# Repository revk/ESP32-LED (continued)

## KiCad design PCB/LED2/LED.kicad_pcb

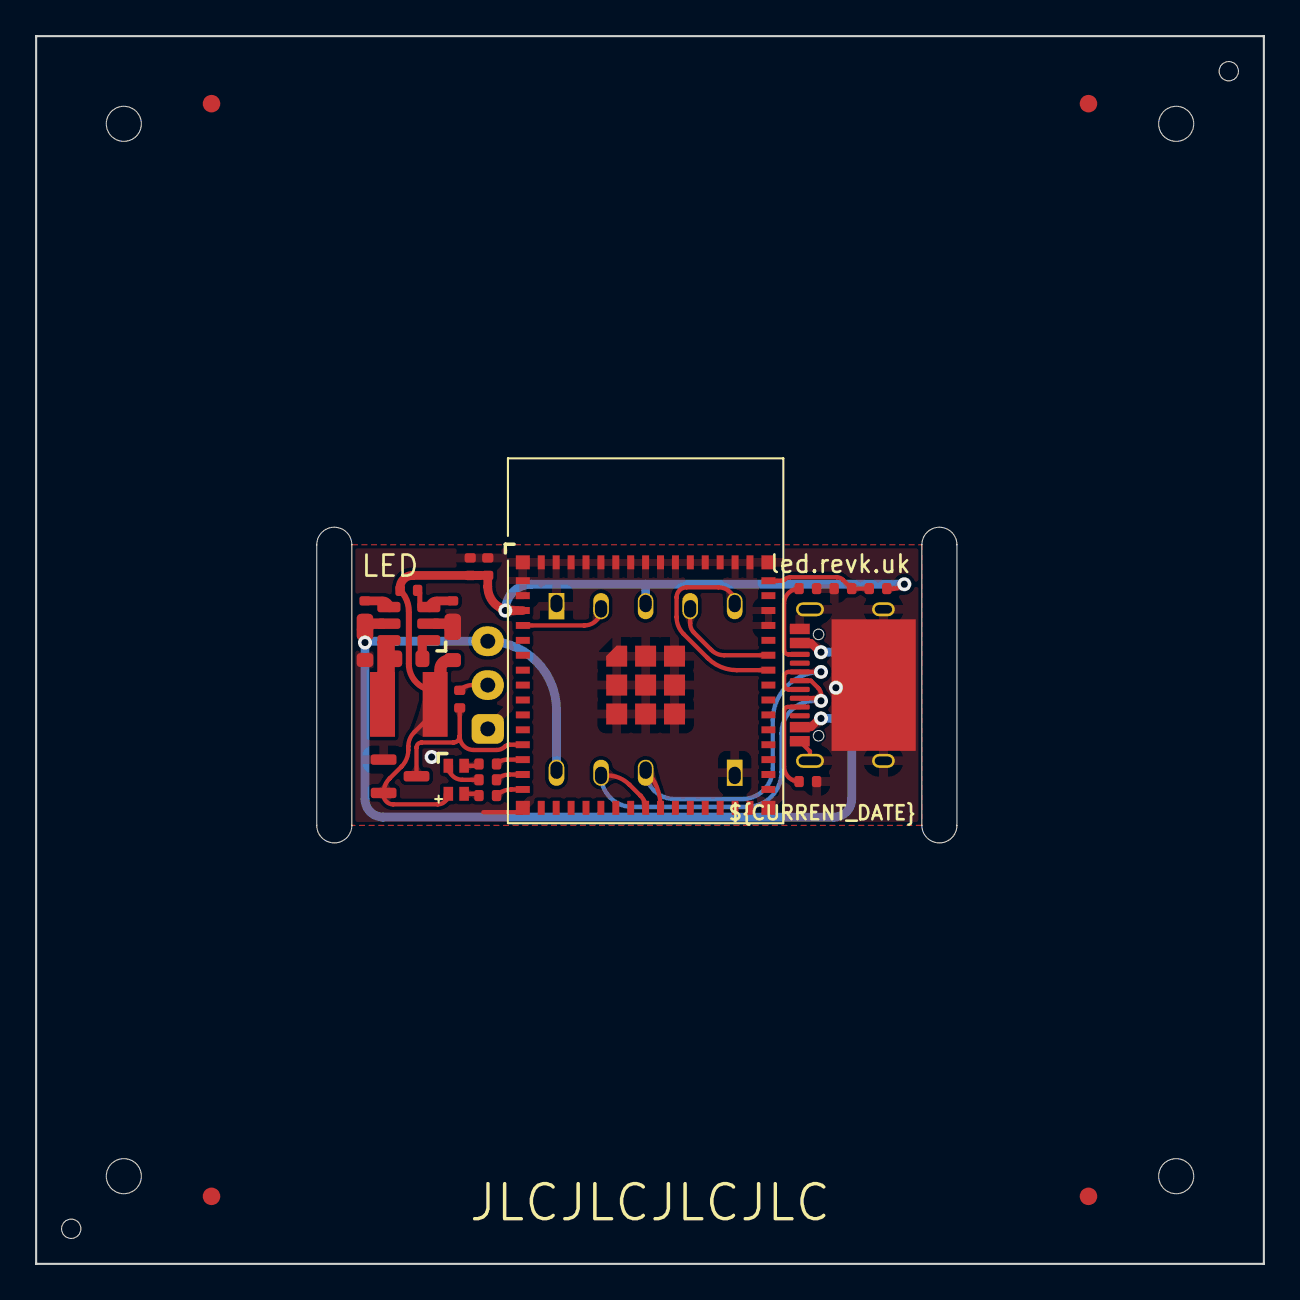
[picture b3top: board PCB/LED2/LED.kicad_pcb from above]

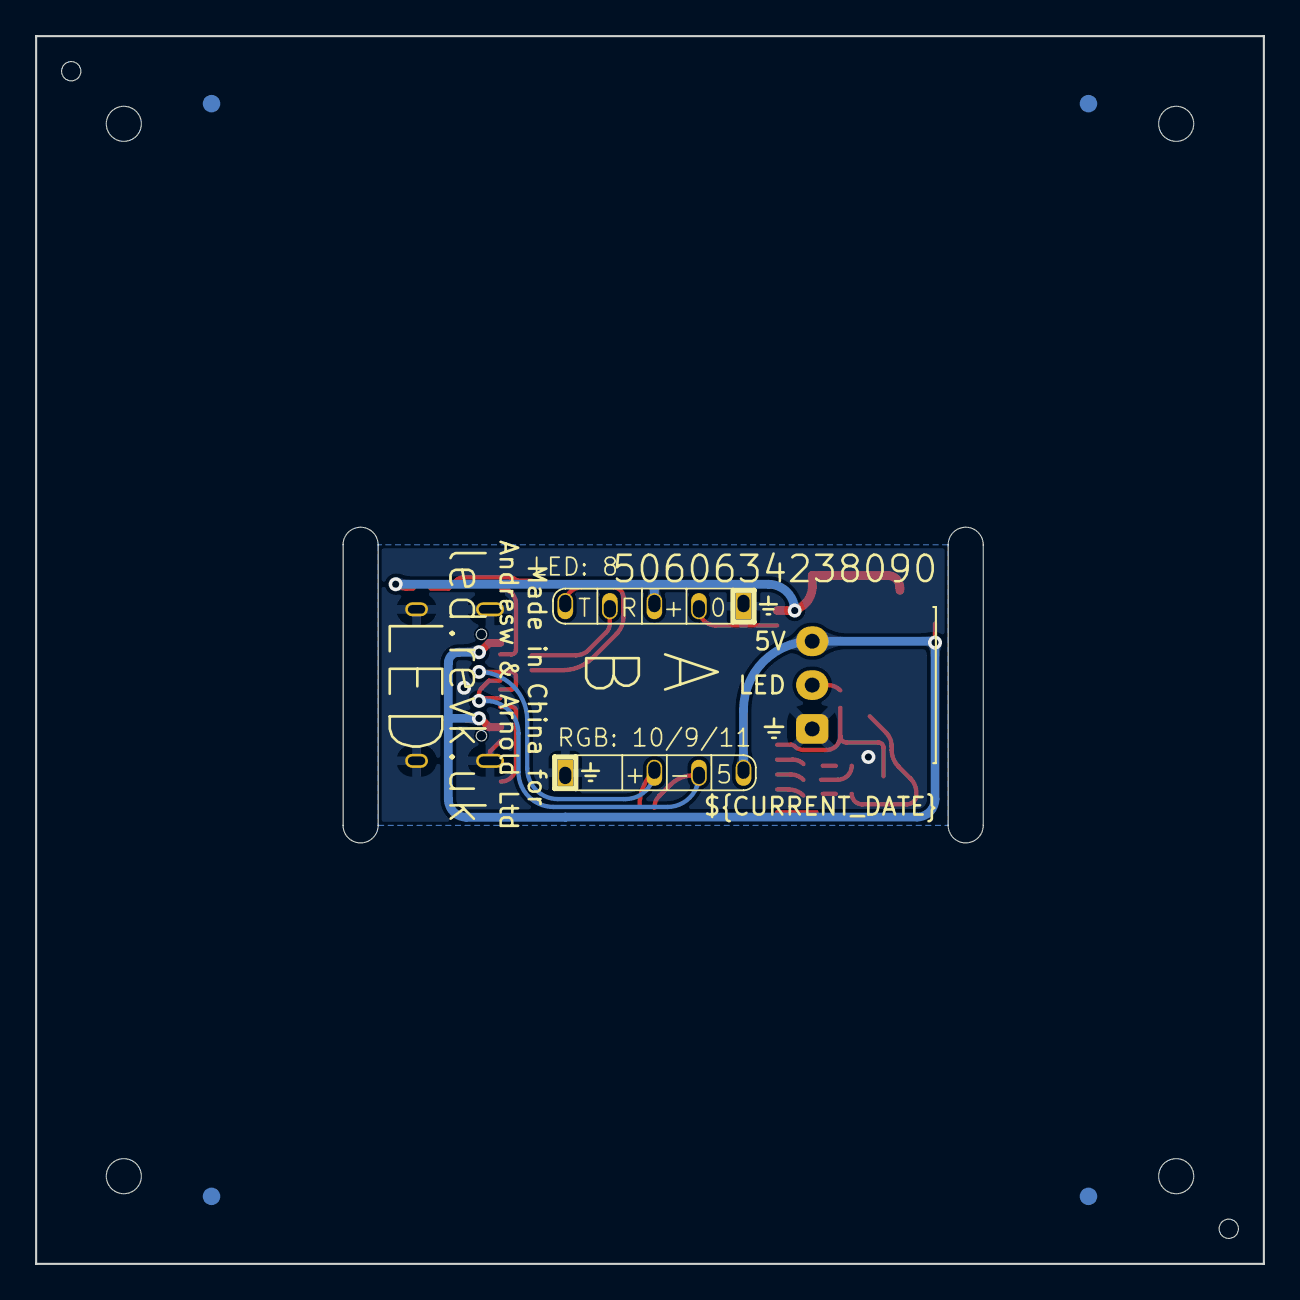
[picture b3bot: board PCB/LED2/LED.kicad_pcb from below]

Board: 2 copper layers, 70.0 x 70.0 mm, 28 parts (3 on the bottom side), 19 nets.

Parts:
C7: 100nF; C_0402
C8: 22uF; C_0402
C9: 1uF; C_0402
C10: 10uF 50V; C_0603_
C11: 10uF 6.3V; C_0603_
C12: 100nF; C_0603_
D2: RGB; LED-RGB-1.6x1.6
D3: BAV99; SOT-23
J1: Conn_01x03; PTSM-HH-3-RA
J2: USB-C; USC16-TR
J3: Shelly
J4: USB-PROG
L2: 10uH; L_4x4_
PCB1: 70x70; PCB7070
R2: 10K; R_0402
R4: 124k; R_0402_
R5, R6: 5K1; R_0402
R7: 100R; R_0402
R8: 680R; R_0402
R11: 2K; R_0402
R12: 220R; R_0402
R14: 39k2; R_0402_
R15: 1M; R_0402_
U6: ESP32-S3-MINI-1
U7: MD8942; SOT-23-6-MD8942
V1, V2: VCUT70

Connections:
+3V3: C7.1, C8.1, D2.4 (A), D3.2 (A), J3.3 (3V3), R2.1, U6.3 (3V3), U7.8 (VOUT)
B: R12.2, U6.15 (GPIO11)
D+: J2.A6 (D+), J2.B6 (D+), J4.3 (D+), U6.24 (GPIO20)
D-: J2.A7 (D-), J2.B7 (D-), J4.2 (D-), U6.23 (GPIO19)
DC: J1.3, J2.A4 (VBUS), J2.A9 (VBUS), J2.B4 (VBUS), J2.B9 (VBUS), J4.1 (VBUS), U7.5 (VIN)
G: R11.2, U6.13 (GPIO9)
GND: C7.2, C8.2, C9.2, D3.1 (K), J1.1, J2.A1 (GND), J2.A12 (GND), J2.B1 (GND), J2.B12 (GND), J2.S1 (SHIELD), J3.1 (GND), J4.4 (GND), R5.2, R6.1, U6.1 (GND), U6.2 (GND), U6.42 (GND), U6.43 (GND), U6.46 (GND), U6.47 (GND), U6.48 (GND), U6.49 (GND), U6.50 (GND), U6.51 (GND), U6.52 (GND), U6.53 (GND), U6.54 (GND), U6.55 (GND), U6.56 (GND), U6.57 (GND), U6.58 (GND), U6.59 (GND), U6.60 (GND), U6.61 (GND), U6.62 (GND), U6.63 (GND), U6.64 (GND), U6.65 (GND), U7.2 (GND), U7.7 (GND)
LED: D3.3 (K), R7.2, U6.12 (GPIO8)
unnamed: D2.3 (BK), R12.1
unnamed: D2.2 (GK), R11.1
unnamed: D2.1 (RK), R8.1
unnamed: J1.2, R7.1
unnamed: J2.A5 (CC1), R5.1
unnamed: J2.B5 (CC2), R6.2
unnamed: J3.2 (0), U6.4 (GPIO0)
unnamed: J3.4 (Rx), U6.40 (GPIO44)
unnamed: J3.5 (Tx), U6.39 (GPIO43)
unnamed: C9.1, R2.2, U6.45 (EN)
R: R8.2, U6.14 (GPIO10)

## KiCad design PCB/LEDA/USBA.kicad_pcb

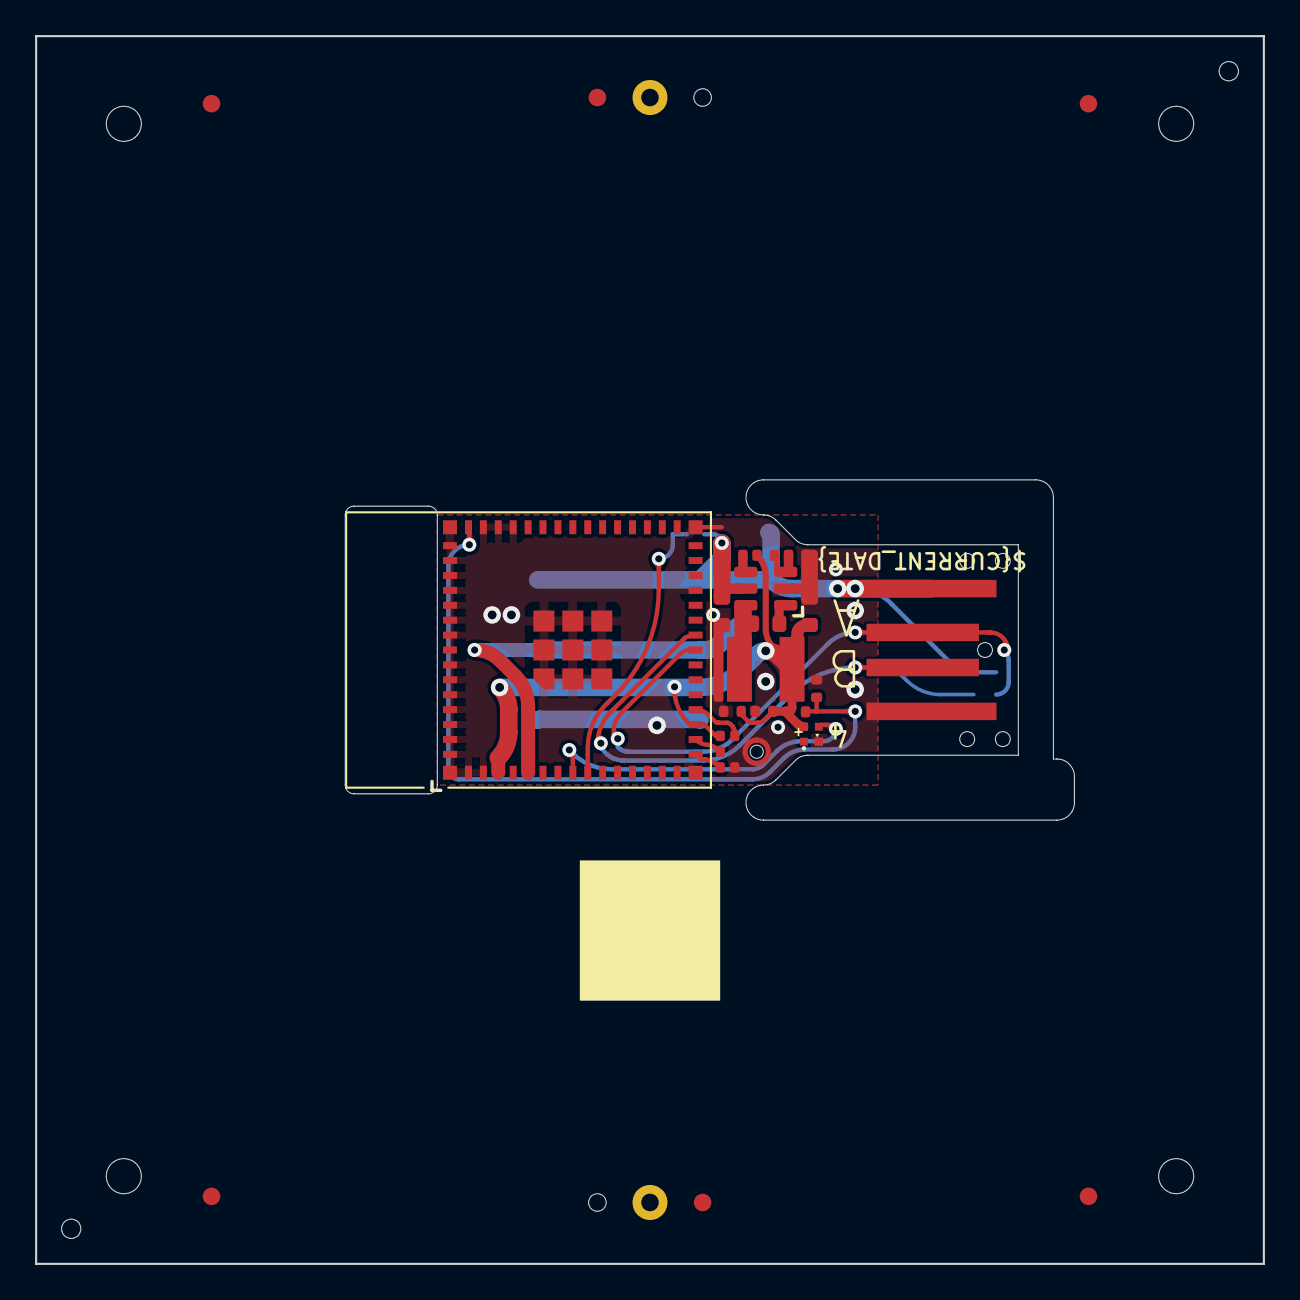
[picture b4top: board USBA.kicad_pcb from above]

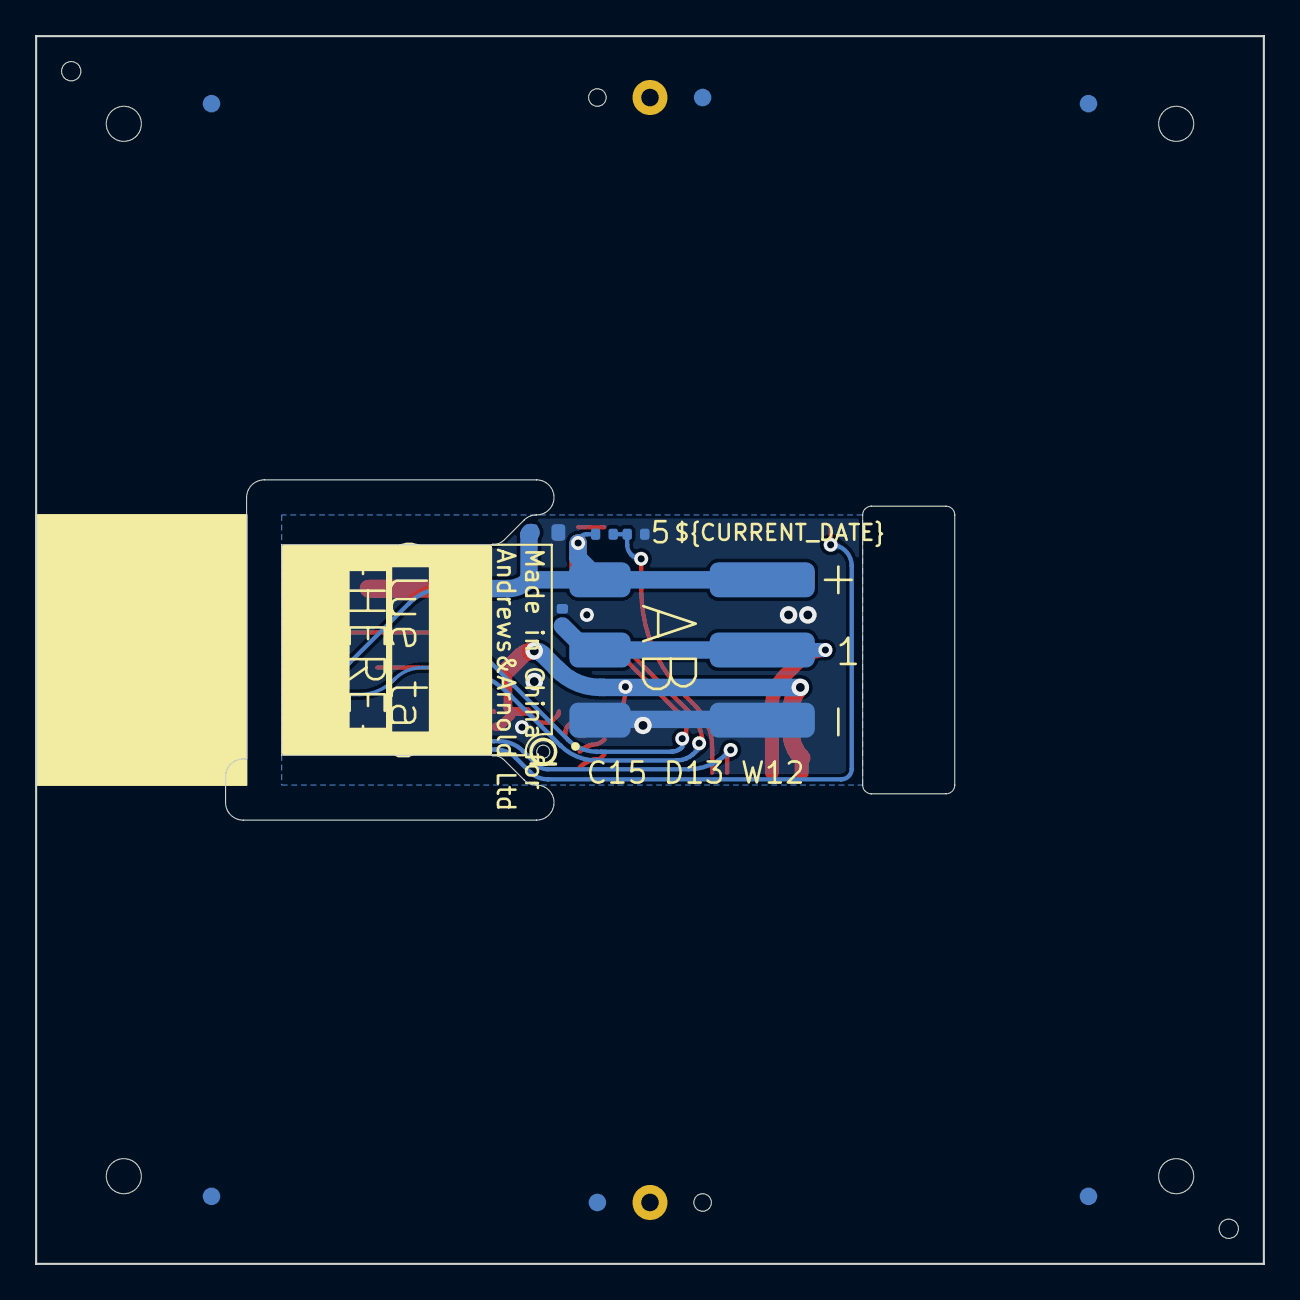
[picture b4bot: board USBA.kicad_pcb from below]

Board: 2 copper layers, 70.0 x 70.0 mm, 25 parts (8 on the bottom side), 12 nets.

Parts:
C1: 100nF; C_0402
C2: 22uF; C_0402
C3: 1uF; C_0402
C4: 10uF 35V; C_0603
C6: 10uF 35V; C_0603_
C7: 10uF 6.3V; C_0603_
C8: 100nF; C_0603_
D1: XL-1010RGBC-WS2812B; SMD1010
D2: DFN1006-2L
J1: USB_A; USB-A-PCB
J2: Conn_01x03; WAGO-2060-453-998-404
J3: TC2030-USB-NL-DS; Tag-Connect_TC2030-IDC-NL_2x03_P1.27mm_Vertical
L2: 10uH; L_4x4_
PCB1: 70x70; PCB7070
R1, R3: 10K; R_0402
R2: 124K; R_0402
R9: 124k; R_0402_
R10: 39k2; R_0402_
R11: 1M; R_0402_
U1: ICS43434_MEMS_Mic
U2: ESP32-S3-MINI-1
U5: MD8942; SOT-23-6-MD8942
V1, V2: 70; VCUT70N

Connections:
+3.3V: C1.1, C2.1, D1.2 (+), R1.1, U1.5 (VDD), U2.3 (3V3), U2.18 (GPIO14), U5.8 (VOUT)
ADC: R2.2, R3.1, U2.9 (GPIO5)
D+: J1.3 (D+), J3.4 (D+), U2.24 (GPIO20)
D-: J1.2 (D-), J3.3 (D-), U2.23 (GPIO19)
DC: C4.1, J1.1 (VBUS), J2.3, J3.1 (VBUS), J3.2 (VBUS), R2.1, U5.5 (VIN)
GND: C1.2, C2.2, C3.2, C4.2, D1.3 (-), D2.1, J1.4 (GND), J2.1, J3.5 (GND), J3.6 (GND), R3.2, U1.2 (LR), U1.3 (GND), U2.1 (GND), U2.2 (GND), U2.27 (GPIO47), U2.42 (GND), U2.43 (GND), U2.44 (GPIO46), U2.46 (GND), U2.47 (GND), U2.48 (GND), U2.49 (GND), U2.50 (GND), U2.51 (GND), U2.52 (GND), U2.53 (GND), U2.54 (GND), U2.55 (GND), U2.56 (GND), U2.57 (GND), U2.58 (GND), U2.59 (GND), U2.60 (GND), U2.61 (GND), U2.62 (GND), U2.63 (GND), U2.64 (GND), U2.65 (GND), U5.2 (GND), U5.7 (GND)
LED1: D1.4 (I), U2.8 (GPIO4)
LED2: D2.2, J2.2, U2.5 (GPIO1)
unnamed: C3.1, R1.2, U2.45 (EN)
SCK: U1.4 (SCK), U2.19 (GPIO15)
SD: U1.6 (SD), U2.17 (GPIO13)
WS: U1.1 (WS), U2.16 (GPIO12)

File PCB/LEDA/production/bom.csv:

Designator,Footprint,Quantity,Value,LCSC Part #
,8abff937-711c-455e-bc8a-c75c5e04b52f,1,,
C1,C_0402,1,100nF,
C2,C_0402,1,22uF,
C3,C_0402,1,1uF,
C4,C_0603,1,10uF 35V,C194427
C6,C_0603_,1,10uF 35V,C194427
C7,C_0603_,1,10uF 6.3V,C1691
C8,C_0603_,1,100nF,
D1,SMD1010,1,XL-1010RGBC-WS2812B,C5349953
D2,DFN1006-2L,1,~,C5137770
J2,WAGO-2060-453-998-404,1,Conn_01x03,C2765056
L2,L_4x4_,1,10uH,
"R1, R3",R_0402,2,10K,
R10,R_0402_,1,39k2,
R11,R_0402_,1,1M,
R2,R_0402,1,124K,
R9,R_0402_,1,124k,
U1,ICS43434_MEMS_Mic,1,ICS43434_MEMS_Mic,C5656610
U2,ESP32-S3-MINI-1,1,ESP32-S3-MINI-1,C3013941
U5,SOT-23-6-MD8942,1,MD8942,C2684786

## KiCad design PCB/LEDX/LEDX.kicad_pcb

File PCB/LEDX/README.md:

# LEDX

## Trademark

This is an open source project, but bear in mind you cannot sell boards or cases bearing the Andrews & Arnold Ltd name, the A&A logo, the registered trademark AJK logo, or the GS1 allocated EANs assigned to Andrews & Arnold Ltd.

## PCB Designs

These files are for use with [KiCAD](https://www.kicad.org).

- [LED](LED.kicad_pro)

## 3D

3D case designs are normally automatically created from the PCB so as to ensure correct details and placement of apertures, etc.

|Design|Bottom|Top|Combined|
|------|------|---|--------|
|LED||||

## PCB Images

---

*Auto generated README.md 2025-11-15T09:00:40*

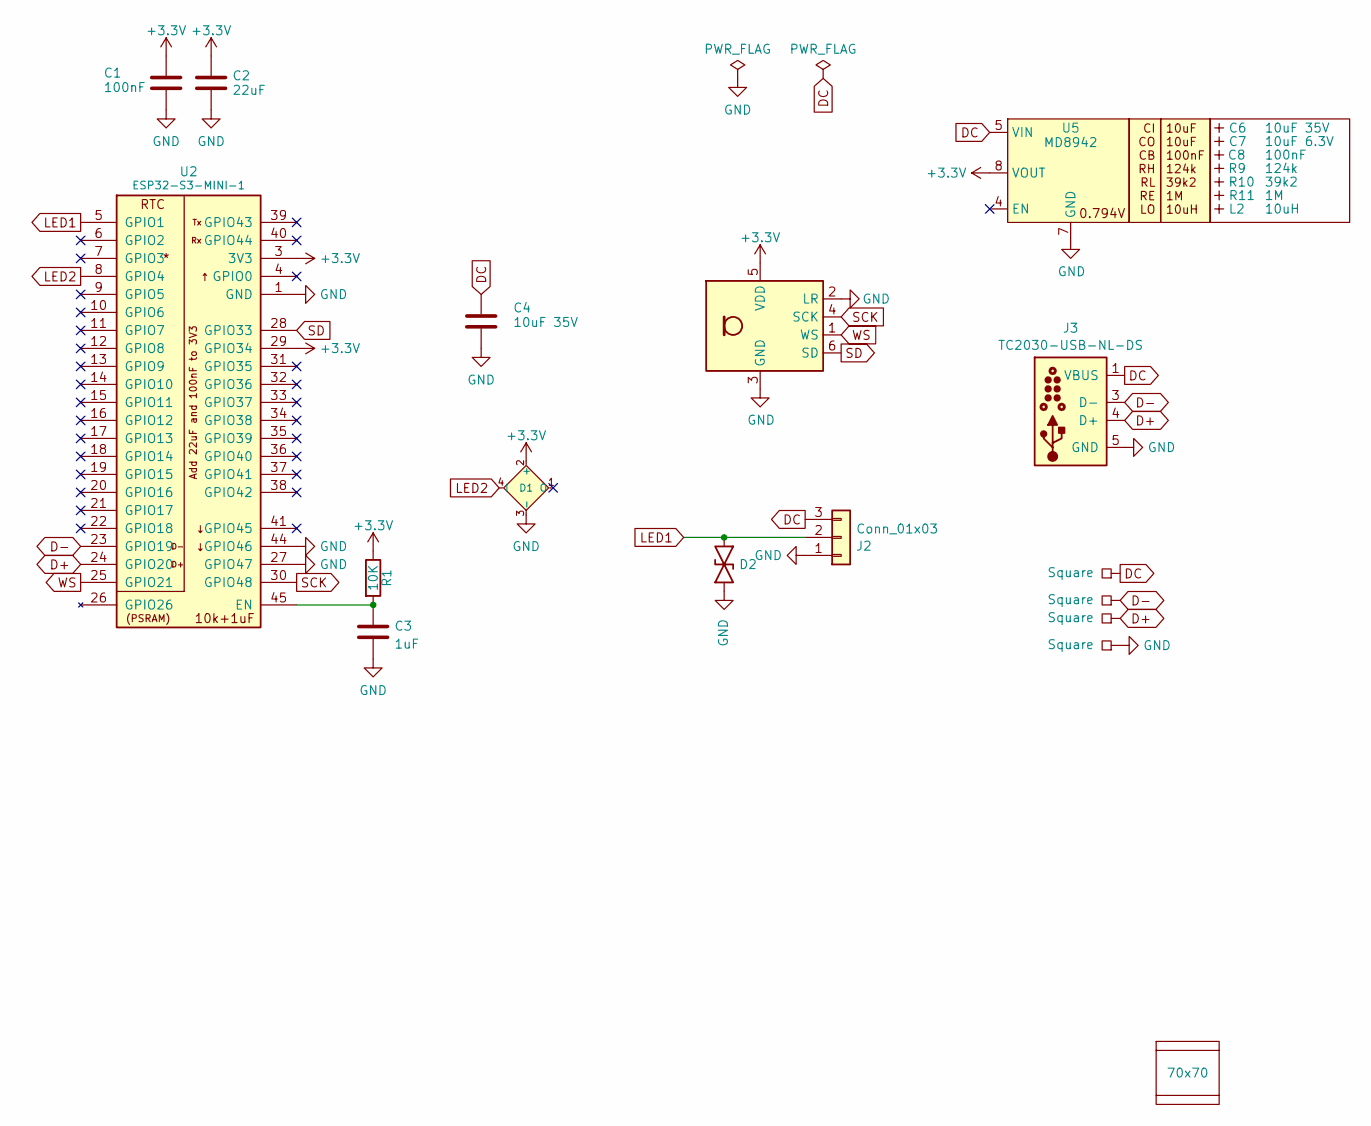
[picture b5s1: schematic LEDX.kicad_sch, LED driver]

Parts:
C1: 100nF; C_0402
C2: 22uF; C_0402
C3: 1uF; C_0402
C4: 10uF 35V; C_0603; LCSC Part # C194427
C6: 10uF 35V; C_0603_; LCSC Part # C194427
C7: 10uF 6.3V; C_0603_; LCSC Part # C1691
C8: 100nF; C_0603_
D1: XL-1010RGBC-WS2812B; SMD1010; LCSC Part # C5349953
D2: DFN1006-2L; LCSC Part # C5137770
J2: Conn_01x03; WAGO-2060-453-998-404; LCSC Part # C2765056
J3: TC2030-USB-NL-DS; Tag-Connect_TC2030-IDC-NL_2x03_P1.27mm_Vertical
L2: 10uH; L_4x4_
P1, P2, P3, P4: Square; PAD-2mm
PCB1: 70x70; PCB7070
R1: 10K; R_0402
R9: 124k; R_0402_
R10: 39k2; R_0402_
R11: 1M; R_0402_
U1: ICS43434_MEMS_Mic; LCSC Part # C5656610
U2: ESP32-S3-MINI-1; LCSC Part # C3013941
U5: MD8942; SOT-23-6-MD8942; LCSC Part # C2684786
V1, V2: 70; VCUT70N

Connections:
+3.3V: C1.1, C2.1, D1.2 (+), R1.1, U1.5 (VDD), U2.3 (3V3), U2.29 (GPIO34), U5.8 (VOUT)
D+: J3.4 (D+), P3.1, U2.24 (GPIO20)
D-: J3.3 (D-), P2.1, U2.23 (GPIO19)
DC: C4.1, J2.3, J3.1 (VBUS), J3.2 (VBUS), P1.1, U5.5 (VIN)
GND: C1.2, C2.2, C3.2, C4.2, D1.3 (-), D2.1, J2.1, J3.5 (GND), J3.6 (GND), P4.1, U1.2 (LR), U1.3 (GND), U2.1 (GND), U2.2 (GND), U2.27 (GPIO47), U2.42 (GND), U2.43 (GND), U2.44 (GPIO46), U2.46 (GND), U2.47 (GND), U2.48 (GND), U2.49 (GND), U2.50 (GND), U2.51 (GND), U2.52 (GND), U2.53 (GND), U2.54 (GND), U2.55 (GND), U2.56 (GND), U2.57 (GND), U2.58 (GND), U2.59 (GND), U2.60 (GND), U2.61 (GND), U2.62 (GND), U2.63 (GND), U2.64 (GND), U2.65 (GND), U5.2 (GND), U5.7 (GND)
LED1: D2.2, J2.2, U2.5 (GPIO1)
LED2: D1.4 (I), U2.8 (GPIO4)
unnamed: C3.1, R1.2, U2.45 (EN)
SCK: U1.4 (SCK), U2.30 (GPIO48)
SD: U1.6 (SD), U2.28 (GPIO33)
WS: U1.1 (WS), U2.25 (GPIO21)

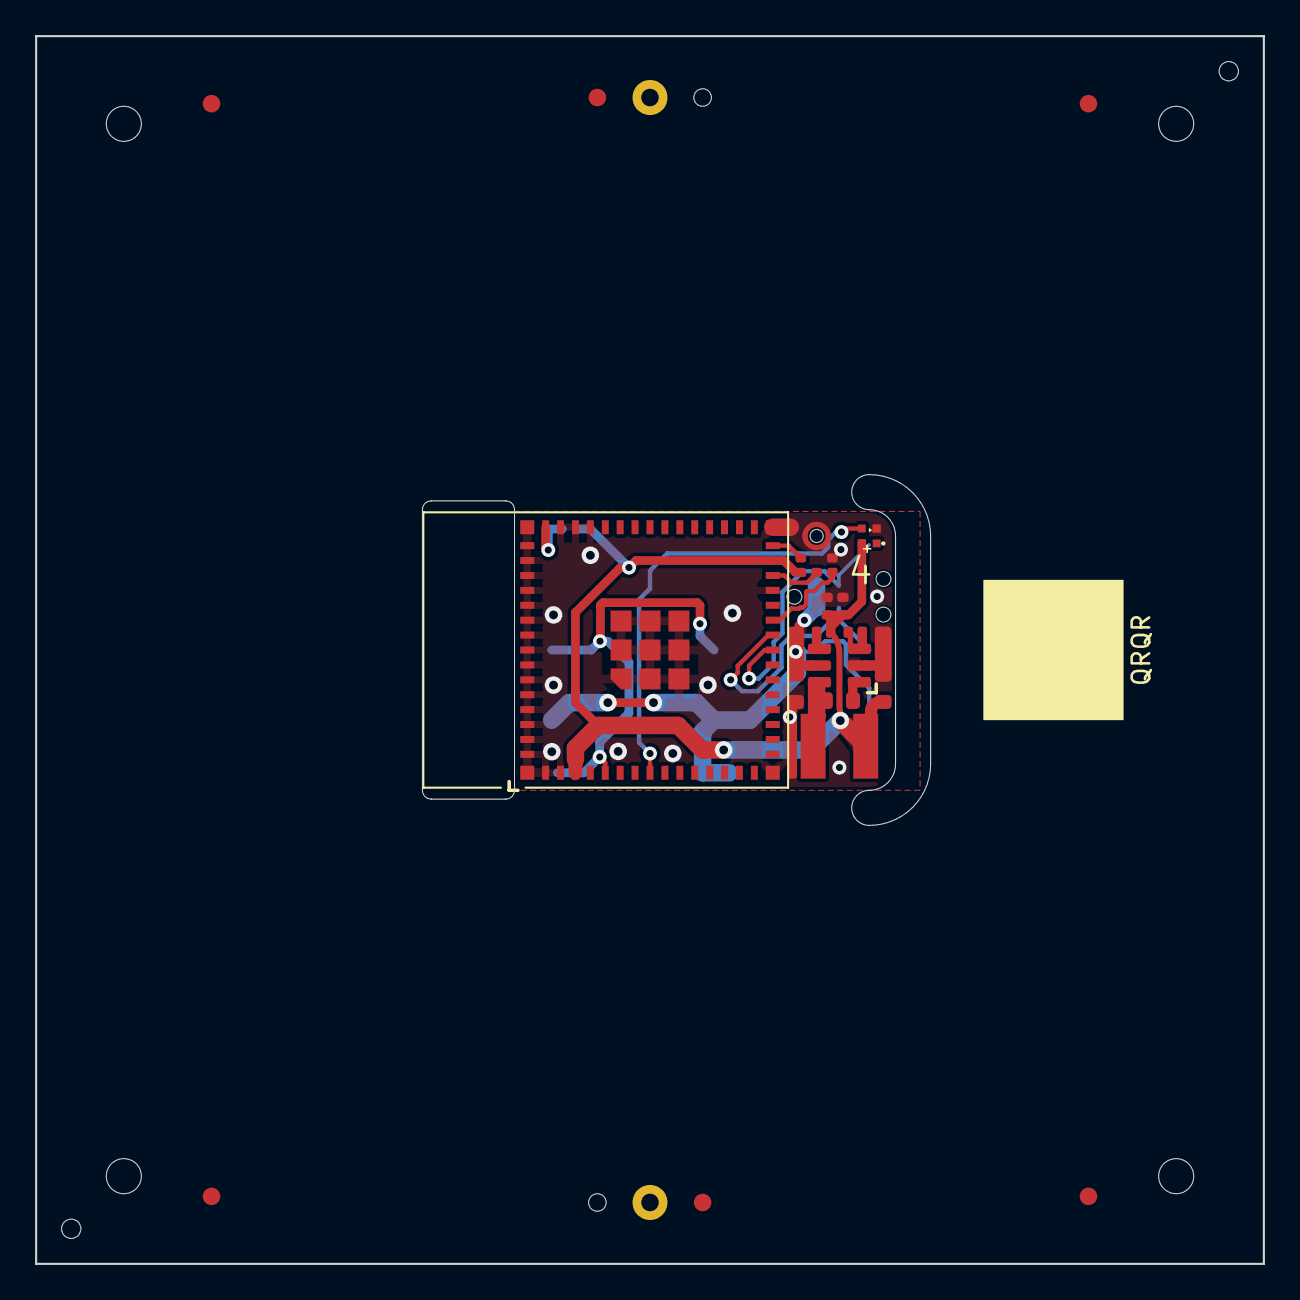
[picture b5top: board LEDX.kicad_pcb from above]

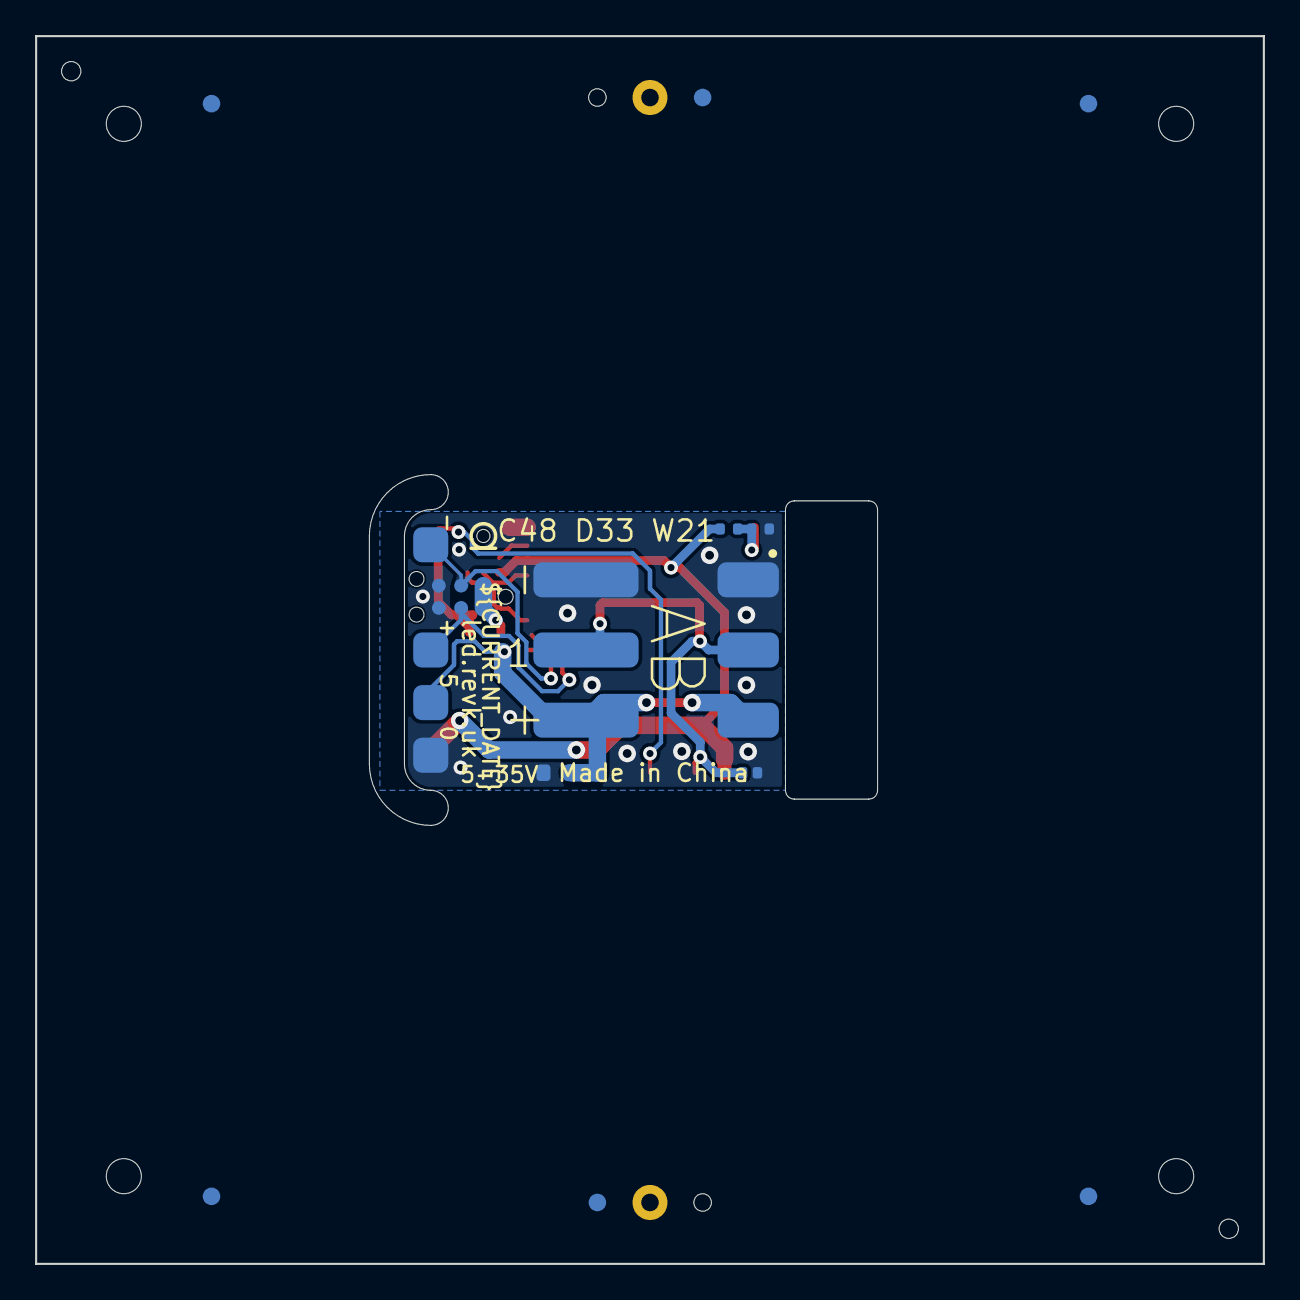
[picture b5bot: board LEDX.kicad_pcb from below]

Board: 2 copper layers, 70.0 x 70.0 mm, 26 parts (12 on the bottom side), 11 nets.

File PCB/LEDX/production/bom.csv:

Designator,Footprint,Quantity,Value,LCSC Part #
C1,C_0402,1,100nF,
C2,C_0402,1,22uF,
C3,C_0402,1,1uF,
C4,C_0603,1,10uF 35V,C194427
C6,C_0603_,1,10uF 35V,C194427
C7,C_0603_,1,10uF 6.3V,C1691
C8,C_0603_,1,100nF,
D1,SMD1010,1,XL-1010RGBC-WS2812B,C5349953
D2,DFN1006-2L,1,~,C5137770
J2,WAGO-2060-453-998-404,1,Conn_01x03,C2765056
L2,L_4x4_,1,10uH,
R1,R_0402,1,10K,
R10,R_0402_,1,39k2,
R11,R_0402_,1,1M,
R9,R_0402_,1,124k,
U1,ICS43434_MEMS_Mic,1,ICS43434_MEMS_Mic,C5656610
U2,ESP32-S3-MINI-1,1,ESP32-S3-MINI-1,C3013941
U5,SOT-23-6-MD8942,1,MD8942,C2684786
